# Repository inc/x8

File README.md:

# X8 computer

## Overview

X8 is a small low-cost low-power computer designed by Lone Dynamics.

## Specifications

| | |
| --- | --- |
| Dimensions | 1in x 1in (25.4mm x 25.4mm) | | | |
| Processor | 8-bit ATmega328PB (2KB SRAM / 32KB Flash) @ 8MHz |
| Memory | 1Mb (128KB) SRAM via SPI @ 4MHz |
| Wireless | ESP-01 WiFi module via UART0 (optional) |
| Display | 128x64 OLED display module via I2C (optional) |
| Power | MicroUSB (1A onboard regulator) |

## Photos

## Pinout

## Schematics

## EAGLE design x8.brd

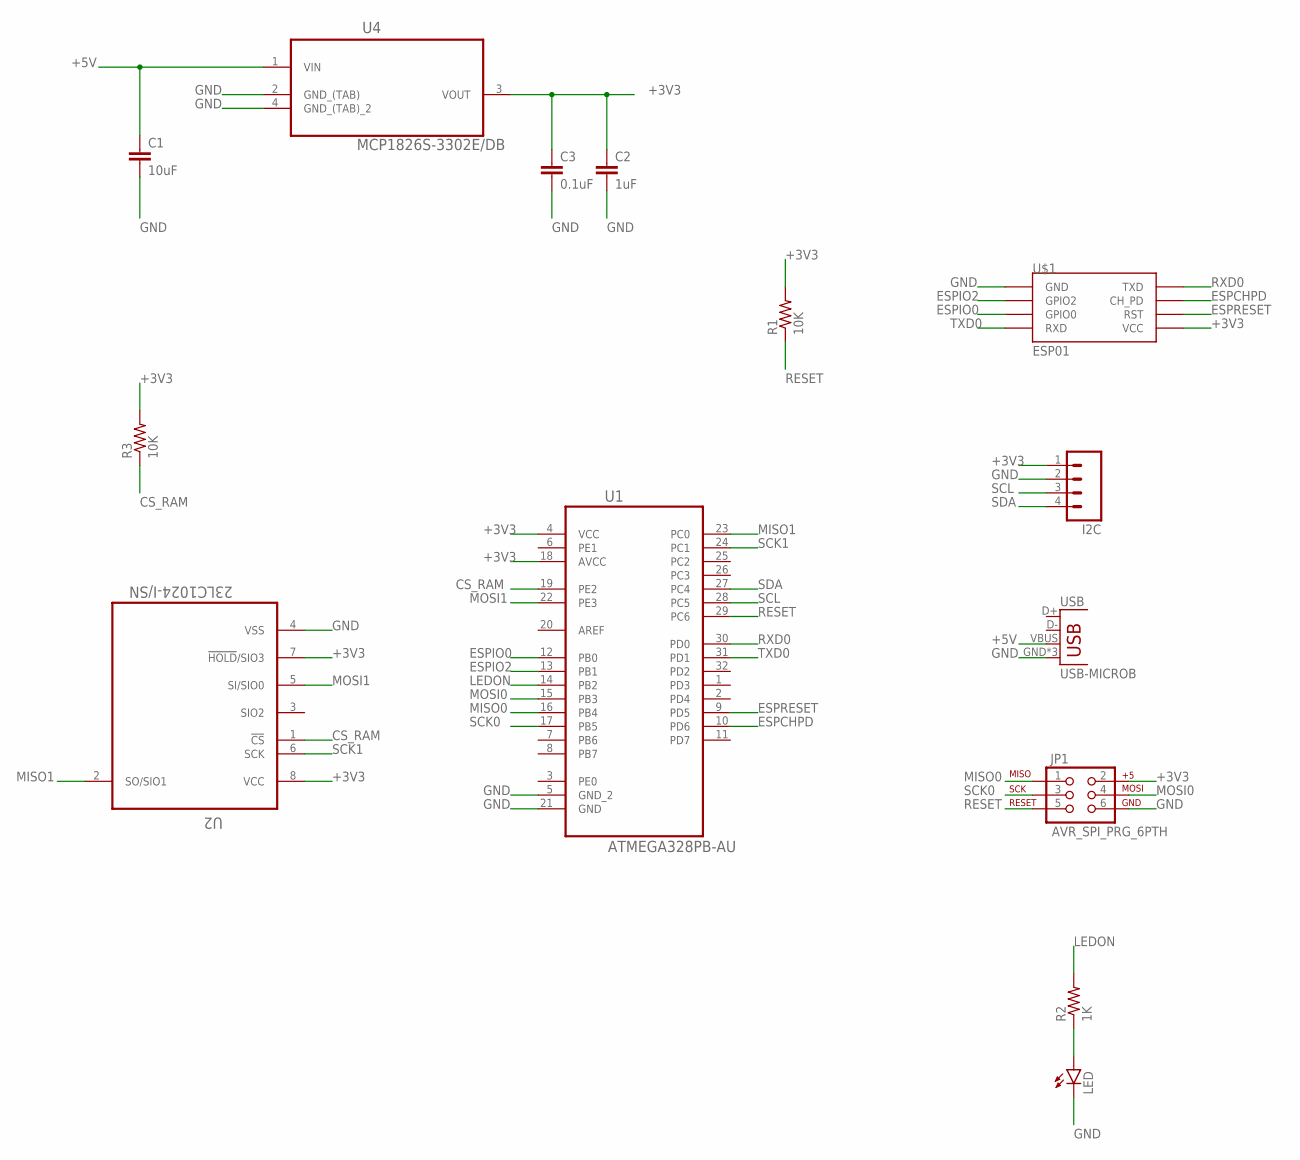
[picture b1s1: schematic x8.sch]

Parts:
C1: 10uF; 0402-CAP
C2: 1uF; 0402-CAP
C3: 0.1uF; 0402-CAP
I2C: M04PTH; 1X04
JP1: AVR_SPI_PRG_6PTH; 2X3
LED: LED0603; LED-0603
R1, R3: 10K; 0402-RES
R2: 1K; 0402-RES
U1: ATMEGA328PB-AU; QFP80P900X900X120-32N
U2: 23LC1024-I/SN; SOIC127P600X175-8N
U4: MCP1826S-3302E/DB; SOT230P700X180-4N
U$1: ESP01
USB: USB-MICROB

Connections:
+3V3: C2.1, C3.1, I2C.1, JP1.2, R1.2, R3.2, U1.4 (VCC), U1.18 (AVCC), U2.7 (!HOLD!/SIO3), U2.8 (VCC), U4.3 (VOUT), U$1.VCC
+5V: C1.1, U4.1 (VIN), USB.VBUS
CS_RAM: R3.1, U1.19 (PE2), U2.1 (!CS)
ESPCHPD: U1.10 (PD6), U$1.CH_PD
ESPIO0: U1.12 (PB0), U$1.GPIO0
ESPIO2: U1.13 (PB1), U$1.GPIO2
ESPRESET: U1.9 (PD5), U$1.RST
GND: C1.2, C2.2, C3.2, I2C.2, JP1.6, LED.C, U1.5 (GND_2), U1.21 (GND), U2.4 (VSS), U4.2 (GND_(TAB)), U4.4 (GND_(TAB)_2), U$1.GND, USB.GND, USB.MT1 (GND), USB.MT2 (GND)
LEDON: R2.2, U1.14 (PB2)
MISO0: JP1.1, U1.16 (PB4)
MISO1: U1.23 (PC0), U2.2 (SO/SIO1)
MOSI0: JP1.4, U1.15 (PB3)
MOSI1: U1.22 (PE3), U2.5 (SI/SIO0)
unnamed: LED.A, R2.1
RESET: JP1.5, R1.1, U1.29 (PC6)
RXD0: U1.30 (PD0), U$1.TX (TXD)
SCK0: JP1.3, U1.17 (PB5)
SCK1: U1.24 (PC1), U2.6 (SCK)
SCL: I2C.3, U1.28 (PC5)
SDA: I2C.4, U1.27 (PC4)
TXD0: U1.31 (PD1), U$1.RX (RXD)

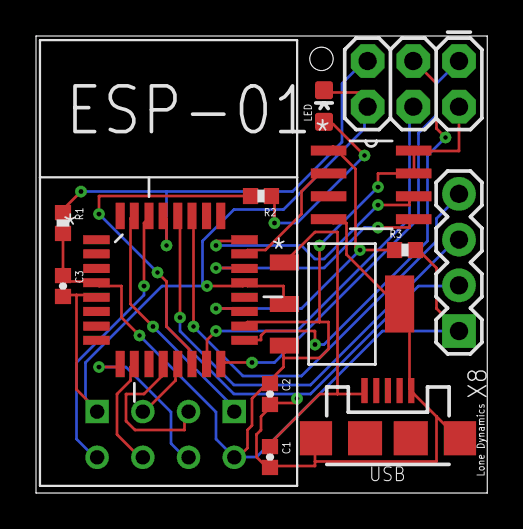
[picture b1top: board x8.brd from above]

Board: 2 copper layers, 25.1 x 25.4 mm, 14 parts (0 on the bottom side), 21 nets.

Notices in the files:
parts and their libraries:
SparkFun-Connectors: Licensing: Creative Commons ShareAlike 4.0 International - https://creativecommons.org/licenses/by-sa/4.0
